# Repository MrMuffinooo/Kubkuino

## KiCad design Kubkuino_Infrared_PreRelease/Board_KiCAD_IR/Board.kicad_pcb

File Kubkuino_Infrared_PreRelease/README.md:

# Specjalizowany czujnik temperaturowy:
## Mikroprocesorowy analizator cieplny

Wersja testowa. Będą zmiany w kodzie i hardware w miarę dostępności części.  

Zrobiłeś kawę albo herbatę i nie chcesz pilnować aż ostygnie? To coś dla Ciebie!
  
Do zrobienia:  
	-Ładniejszy interfejs,  
	-Naprawa wskaźników temperatury  
	-Rozróżnianie HELLO_STD od HELLO_IR (GY-906)  
	-Zmiana wyświetlacza na SSD1306 128x32 (i2c)  
	
Arduino:  
  
	Kod:  
		#define _NAME (String)"[NAZWA]" - Ustawia nazwę jako domyślną  
		#define _PASS (String)"[4 cyfry]" - Ustawia wpisane cyfry jako hasło do parowania  
		#define TONE [TON] - Dźwięk alarmu (uzupełnić na podstawie vars.h)  
		#define ALARM_TIME [milisekundy] - Ile milisekund Arduino ma piszczeć  
  
	Komendy:  
		X - Pierwszy argument  
		Y - Drugi argument  
  
		e; - Nawiązanie połączenia (zwraca "HELLO_IR\r\n") MUSI ZOSTAĆ WYSŁANE  
		qquit; - Rozłączenie MUSI ZOSTAĆ WYSŁANE (specjanie takie długie - na wypadek błędu komunikacji,  
			który wysyła 'q' zamiast 'r'. Nie wiem czemu.)  
		CXX.X; - Ustawienie temperatury zimna  
		HXX.X; - Ustawienie temperatury ciepła  
			C?;/H?; - sprawdzenie temperatur  
		S[komenda AT]; - Przesyła komendę AT do modułu Bluetooth. Zwraca odpowiedź modułu.  
		d; - Reset modułu Bluetooth, ustawienie domyślnej nazwy i hasła  
		r - Zwraca bieżący odczyt z czujnika  
		t; - Zwraca stan jako char (H - Hot, R - Ready, C - Cold)  
		DXY; - Moduł zarządzania komponentami:  
			0Y* - LCD (1 - włącz, 0 - wyłącz)  
			1Y* - Podswietlenie (1 - włącz, 0 - wyłącz)  
			2Y - BT (1 - włącz, 0 - wyłącz)  
			3Y* - LED (1 - włącz, 0 - wyłącz)  
			4Y* - Wyciszenie (1 - wyciszony, 0 - głośny)  
			6 - Status LCD, Podświetlenie, LED, Alarm (1 - włączony, 0 - wyłączony)  
			8 - Przejście w tryb uśpienia  
  
		*Jak jako argument poda się znak zapytania (?) zostanie zwrócony stan pojedynczego modułu  
  
Każda komenda jest zakończona średnikiem ';'!

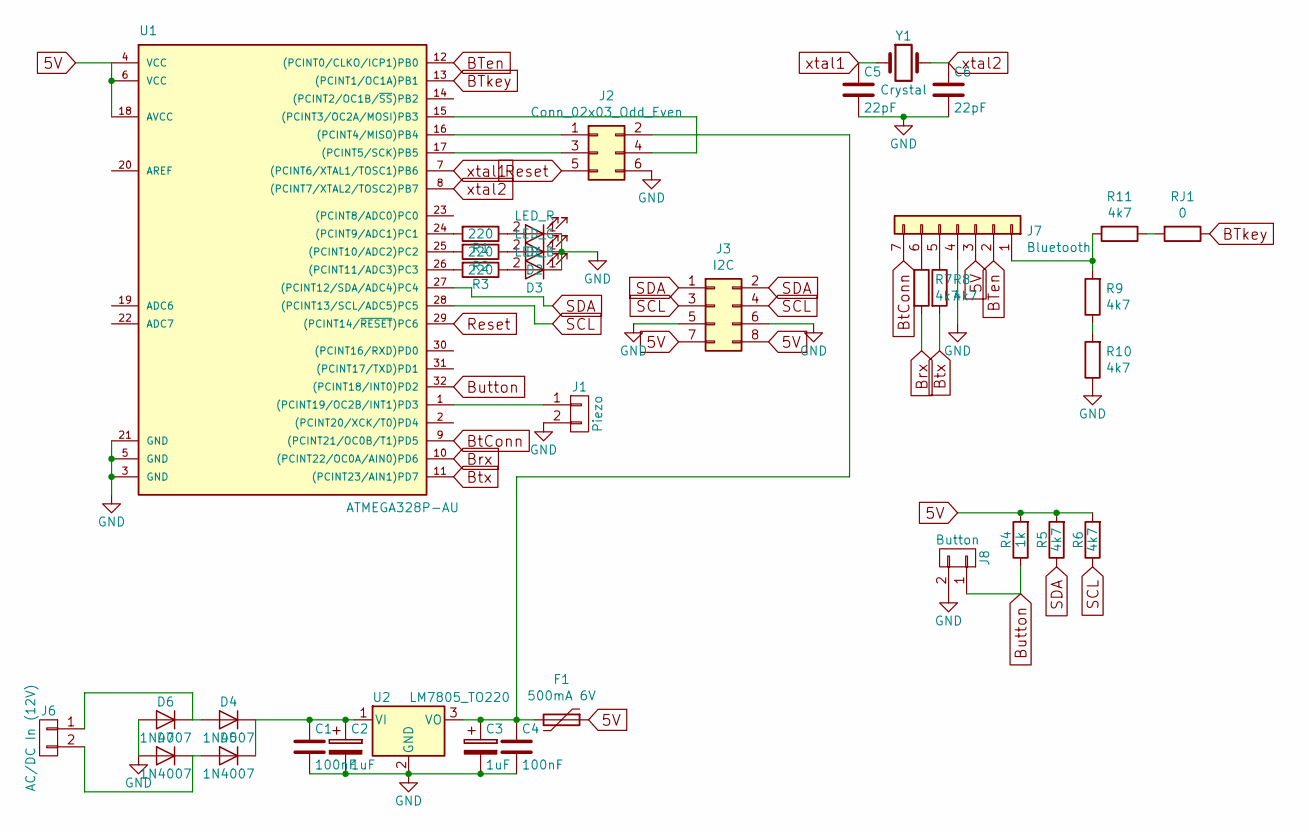
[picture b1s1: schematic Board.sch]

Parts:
C1, C4: 100nF; C_1206
C2, C3: 1uF; CP_Tantalum_Case-A_EIA-3216-18_Hand
C5, C6: 22pF; C_0805_HandSoldering
D1: LED_R; LED_1206
D2: LED_G; LED_1206
D3: LED_B; LED_1206
D4, D5, D6, D7: 1N4007; D_SMA
F1: 500mA 6V; SMD-1206_Pol
J1: Piezo; Pin_Header_Straight_1x02_Pitch2.54mm_SMD_Pin1Left
J2: Conn_02x03_Odd_Even; Pin_Header_Straight_2x03_Pitch2.54mm
J3: I2C; Socket_Strip_Straight_2x04_Pitch2.54mm_SMD
J6: AC/DC In (12V); Socket_Strip_Angled_1x02_Pitch2.54mm
J7: Bluetooth; Pin_Header_Straight_1x07_Pitch2.54mm_SMD_Pin1Left
J8: Button; Pin_Header_Straight_1x02_Pitch2.54mm_SMD_Pin1Left
R1, R2, R3: 220; R_1206
R4: 1k; R_1206
R5, R6, R7, R8, R9, R10, R11: 4k7; R_1206
RJ1: 0; R_1206
U1: ATMEGA328P-AU; TQFP-32_7x7mm_Pitch0.8mm
U2: LM7805_TO220; TO-252-2
Y1: Crystal; Crystal_SMD_HC49-SD_HandSoldering

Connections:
5V: F1.1, J3.7, J3.8, J7.3, R4.2, R5.2, R6.2, U1.4 (VCC), U1.6 (VCC), U1.18 (AVCC)
BTen: J7.2, U1.12 ((PCINT0/CLKO/ICP1)PB0)
BTkey: RJ1.1, U1.13 ((PCINT1/OC1A)PB1)
Brx: R7.2, U1.10 ((PCINT22/OC0A/AIN0)PD6)
BtConn: J7.7, U1.9 ((PCINT21/OC0B/T1)PD5)
Btx: R8.2, U1.11 ((PCINT23/AIN1)PD7)
Button: J8.1, R4.1, U1.32 ((PCINT18/INT0)PD2)
GND: C1.2, C2.2, C3.2, C4.2, C5.2, C6.2, D1.1 (K), D2.1 (K), D3.1 (K), D6.2 (A), D7.2 (A), J1.2, J2.6, J3.5, J3.6, J7.4, J8.2, R10.1, U1.3 (GND), U1.5 (GND), U1.21 (GND), U2.2 (GND)
unnamed: C1.1, C2.1, D4.1 (K), D5.1 (K), U2.1 (VI)
unnamed: C3.1, C4.1, F1.2, J2.2, U2.3 (VO)
unnamed: D1.2 (A), R1.1
unnamed: D2.2 (A), R2.1
unnamed: D3.2 (A), R3.1
unnamed: D4.2 (A), D6.1 (K), J6.1
unnamed: D5.2 (A), D7.1 (K), J6.2
unnamed: J1.1, U1.1 ((PCINT19/OC2B/INT1)PD3)
unnamed: J2.1, U1.16 ((PCINT4/MISO)PB4)
unnamed: J2.3, U1.17 ((PCINT5/SCK)PB5)
unnamed: J2.4, U1.15 ((PCINT3/OC2A/MOSI)PB3)
unnamed: J7.1, R9.2, R11.2
unnamed: J7.5, R8.1
unnamed: J7.6, R7.1
unnamed: R1.2, U1.24 ((PCINT9/ADC1)PC1)
unnamed: R2.2, U1.25 ((PCINT10/ADC2)PC2)
unnamed: R3.2, U1.26 ((PCINT11/ADC3)PC3)
unnamed: R9.1, R10.2
unnamed: R11.1, RJ1.2
Reset: J2.5, U1.29 ((PCINT14/~RESET~)PC6)
SCL: J3.3, J3.4, R6.1, U1.28 ((PCINT13/SCL/ADC5)PC5)
SDA: J3.1, J3.2, R5.1, U1.27 ((PCINT12/SDA/ADC4)PC4)
xtal1: C5.1, U1.7 ((PCINT6/XTAL1/TOSC1)PB6), Y1.1
xtal2: C6.1, U1.8 ((PCINT7/XTAL2/TOSC2)PB7), Y1.2

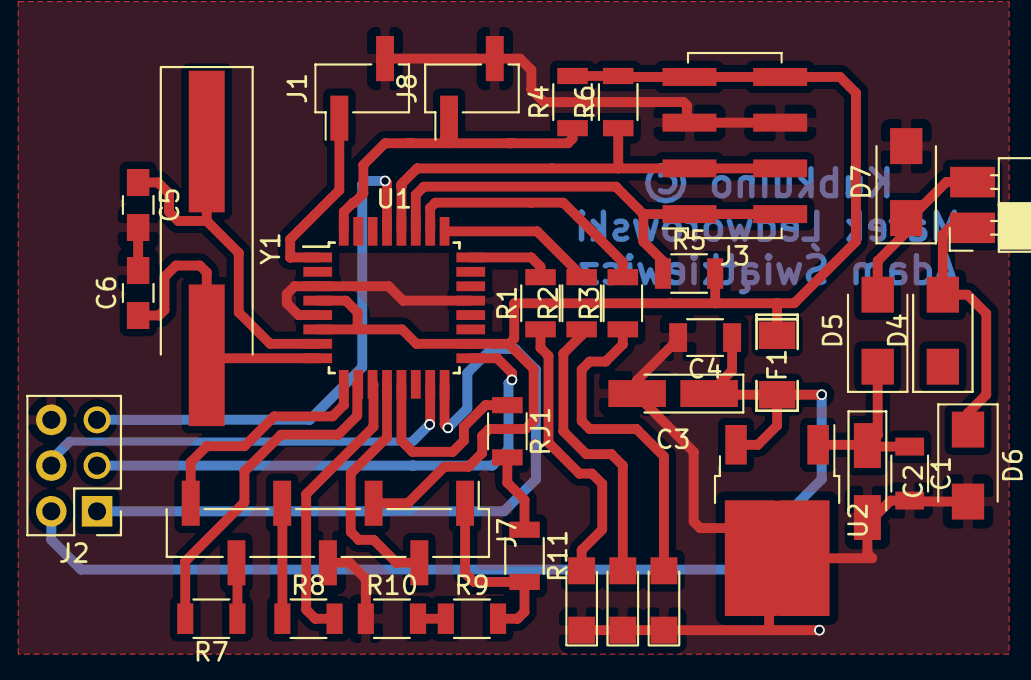
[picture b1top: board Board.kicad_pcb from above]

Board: 2 copper layers, 35 parts (0 on the bottom side), 32 nets.

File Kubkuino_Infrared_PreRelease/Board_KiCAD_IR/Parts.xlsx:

Oznaczenie | Wartość | Obudowa | Notes
C1 | 100nF | 1206
C2 | 1uF | A | (Tantalowy)
C3 | 1uF | A | (Tantalowy)
C4 | 100nF | 1206
C5 | 22pF | 0805
C6 | 22pF | 0805
D1 | 1N4007 | SMA
D2 | 1N4007 | SMA
D3 | 1N4007 | SMA
D4 | 1N4007 | SMA
D7 | LED_R | 1206
D8 | LED_G | 1206
D9 | LED_B | 1206
J1 | Piezo | Goldpin 1x2 żeński
J2 | AC/DC In (12V) | Goldpin 1x2 żeński
J3 | Prog | Goldpin 2x3 męski
J4 | Czujnik | Goldpin 1x4 żeński | GY-906
J6 | LCD | Goldpin 1x4 żeński | SSD1306 32x128 mono
J7 | Button | Goldpin 1x2 żeński
J8 | Bluetooth | Goldpin 1x6 żeński | HC-05 z wyprowadzeniami
Q1 | S8050 | TO-92
R1 | 220 | 1206
R2 | 220 | 1206
R3 | 220 | 1206
R4 | 1k | 1206
R5 | 1k | 1206
R6 | 4k7 | 1206
R7 | 4k7 | 1206
RJ1 | 0 | 1206
RJ2 | 0 | 1206
SW1 | Reset | 6mm x 6mm
U1 | LM7805_TO220 | TO-263-2
U2 | ATMEGA328P-PU | TQFP32
Y1 | Crystal | HC49 | 16MHz

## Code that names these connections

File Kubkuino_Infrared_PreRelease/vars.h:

//Stare
#define ctl 2 //Przycisk
#define buzz 3 //Buzzer
#define btpow 4 //Zasilanie BT
#define btx 5 //Bluetooth TX
#define brx 6 //Bluetooth RX
#define btkey 7 //Bt Key
#define rled A1
#define gled A2
#define bled A3
//Nowe
/*#define ctl 2 //Przycisk
  #define buzz 3 //Buzzer
  #define btpow 9 //Zasilanie BT
  #define btx 7 //Bluetooth TX
  #define brx 5 //Bluetooth RX
  #define btconn 6 //BT connected
  #define btkey 8 //BT Key
  #define rled A1
  #define gled A2
  #define bled A3*/
#if F_CPU != 16000000
#undef F_CPU
#define F_CPU 16000000
#endif

#if (SSD1306_LCDHEIGHT != 64)
#error("Height incorrect, please fix Adafruit_SSD1306.h!");
#endif

/* Pomiary */
int hot, cold;
double pomiar = 0, poppomiar = 0;

/* Bluetooth */
bool conn = false; //Polaczony?

/* Alarm */
uint8_t alarmState = 0b000;
bool glosny = false; //Czy ma piszczec?

/* Zasilanie */
bool lcdon = true;
bool ledon = true;
bool dimlcd = false;

PROGMEM const uint8_t icon[] = { //Bluetooth
  0b00000011, 0b00000000,
  0b00000011, 0b11000000,
  0b00000011, 0b11000000,
  0b00110011, 0b00110000,
  0b00110011, 0b00001100,
  0b00001111, 0b00001100,
  0b00001111, 0b00110000,
  0b00000011, 0b11000000,
  0b00000011, 0b11000000,
  0b00001111, 0b00110000,
  0b00001111, 0b00001100,
  0b00110011, 0b00001100,
  0b00110011, 0b00110000,
  0b00000011, 0b11000000,
  0b00000011, 0b11000000,
  0b00000011, 0b00000000
};

PROGMEM const uint8_t state_hot[] = {
  0b00000110, 0b00000110, 0b01111000,
  0b00000110, 0b00000110, 0b01111000,
  0b00011110, 0b01111000, 0b00011000,
  0b00011110, 0b01111000, 0b00011000,
  0b01111000, 0b00011000, 0b01111000,
  0b01111000, 0b00011000, 0b01111000,
  0b01111000, 0b00011000, 0b01100000,
  0b01111000, 0b00011000, 0b01100000,
  0b00011110, 0b00000000, 0b01100000,
  0b00011110, 0b00000000, 0b01100000,
  0b00011110, 0b00011110, 0b01111000,
  0b00011110, 0b00011110, 0b01111000,
  0b01111000, 0b01111000, 0b00011110,
  0b01111000, 0b01111000, 0b00011110,
  0b00000000, 0b00011000, 0b00000000,
  0b00000000, 0b00011000, 0b00000000,
};

PROGMEM const uint8_t state_ready[] = {
  0b00000000, 0b00000000, 0b00110000,
  0b00000000, 0b00000000, 0b00110000,
  0b00000000, 0b00000000, 0b11111100,
  0b00000000, 0b00000000, 0b11111100,
  0b00000000, 0b00000011, 0b11110000,
  0b00000000, 0b00000011, 0b11110000,
  0b00000000, 0b00001111, 0b11000000,
  0b00000000, 0b00001111, 0b11000000,
  0b00001100, 0b00111111, 0b00000000,
  0b00001100, 0b00111111, 0b00000000,
  0b00111111, 0b11111100, 0b00000000,
  0b00111111, 0b11111100, 0b00000000,
  0b00001111, 0b11110000, 0b00000000,
  0b00001111, 0b11110000, 0b00000000,
  0b00000011, 0b11000000, 0b00000000,
  0b00000011, 0b11000000, 0b00000000,
};

PROGMEM const uint8_t state_cold[] = {
  0b00000000, 0b00000000, 0b00000000,
  0b00000000, 0b00000000, 0b00000000,
  0b00000111, 0b10000001, 0b11100000,
  0b00000111, 0b10000001, 0b11100000,
  0b00000111, 0b10000001, 0b11100000,
  0b00000111, 0b10000001, 0b11100000,
  0b00000000, 0b00000000, 0b00000000,
  0b00000000, 0b00000000, 0b00000000,
  0b00000001, 0b11111111, 0b10000000,
  0b00000001, 0b11111111, 0b10000000,
  0b00000111, 0b11111111, 0b11100000,
  0b00000111, 0b11111111, 0b11100000,
  0b00000111, 0b10000001, 0b11100000,
  0b00000111, 0b10000001, 0b11100000,
  0b00000000, 0b00000000, 0b00000000,
  0b00000000, 0b00000000, 0b00000000,
};

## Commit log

2017-11-05 Preparing collabroation
2017-11-05 added parts list
2017-11-06 cleaning, organizing
    added DEBUG option during compilation
    splashscreen
    parts with prices (PL)
    slight board changes
2017-11-12 Updates
    Finished new board
    Changed SSD1306 to 128x64
    Major RAM optimization
    Main routine optimizations
    Set up display layout
